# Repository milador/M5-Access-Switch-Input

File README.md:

# M5-Access-Switch-Input

A Bluetooth enabled Adaptive Switch Interface based on ESP32 M5StickC/M5StickCPlus, and the Switch Input module which offers up to two 3.5mm switch inputs. 

The Adaptive Switch Interface includes 4 operating modes: 

    1. Switch Mode
    2. Switch Mac Mode  
    3. Morse Keyboard Mode 
    4. Media Control Mode
    5. Settings Mode
	
The mode can be changed by pressing and holding Switch A for 4 seconds or pressing M5 button.

## Requirements and setup instructions 
The setup process is divided to three main catagories:

  1. [Hardware](./Hardware/) : The required hardware and design files
  2. [Software](./Software/) : The required software
  3. [Documentation](./Documentation/) : The assembly guide,user guide and other documents 

## License

### MIT License

Copyright (c) 2022 milador

Permission is hereby granted, free of charge, to any person obtaining a copy of this software and associated documentation files (the "Software"), to deal in the Software without restriction, including without limitation the rights to use, copy, modify, merge, publish, distribute, sublicense, and/or sell copies of the Software, and to permit persons to whom the Software is furnished to do so, subject to the following conditions:

The above copyright notice and this permission notice shall be included in all copies or substantial portions of the Software.

THE SOFTWARE IS PROVIDED "AS IS", WITHOUT WARRANTY OF ANY KIND, EXPRESS OR IMPLIED, INCLUDING BUT NOT LIMITED TO THE WARRANTIES OF MERCHANTABILITY, FITNESS FOR A PARTICULAR PURPOSE AND NONINFRINGEMENT. IN NO EVENT SHALL THE AUTHORS OR COPYRIGHT HOLDERS BE LIABLE FOR ANY CLAIM, DAMAGES OR OTHER LIABILITY, WHETHER IN AN ACTION OF CONTRACT, TORT OR OTHERWISE, ARISING FROM, OUT OF OR IN CONNECTION WITH THE SOFTWARE OR THE USE OR OTHER DEALINGS IN THE SOFTWARE.

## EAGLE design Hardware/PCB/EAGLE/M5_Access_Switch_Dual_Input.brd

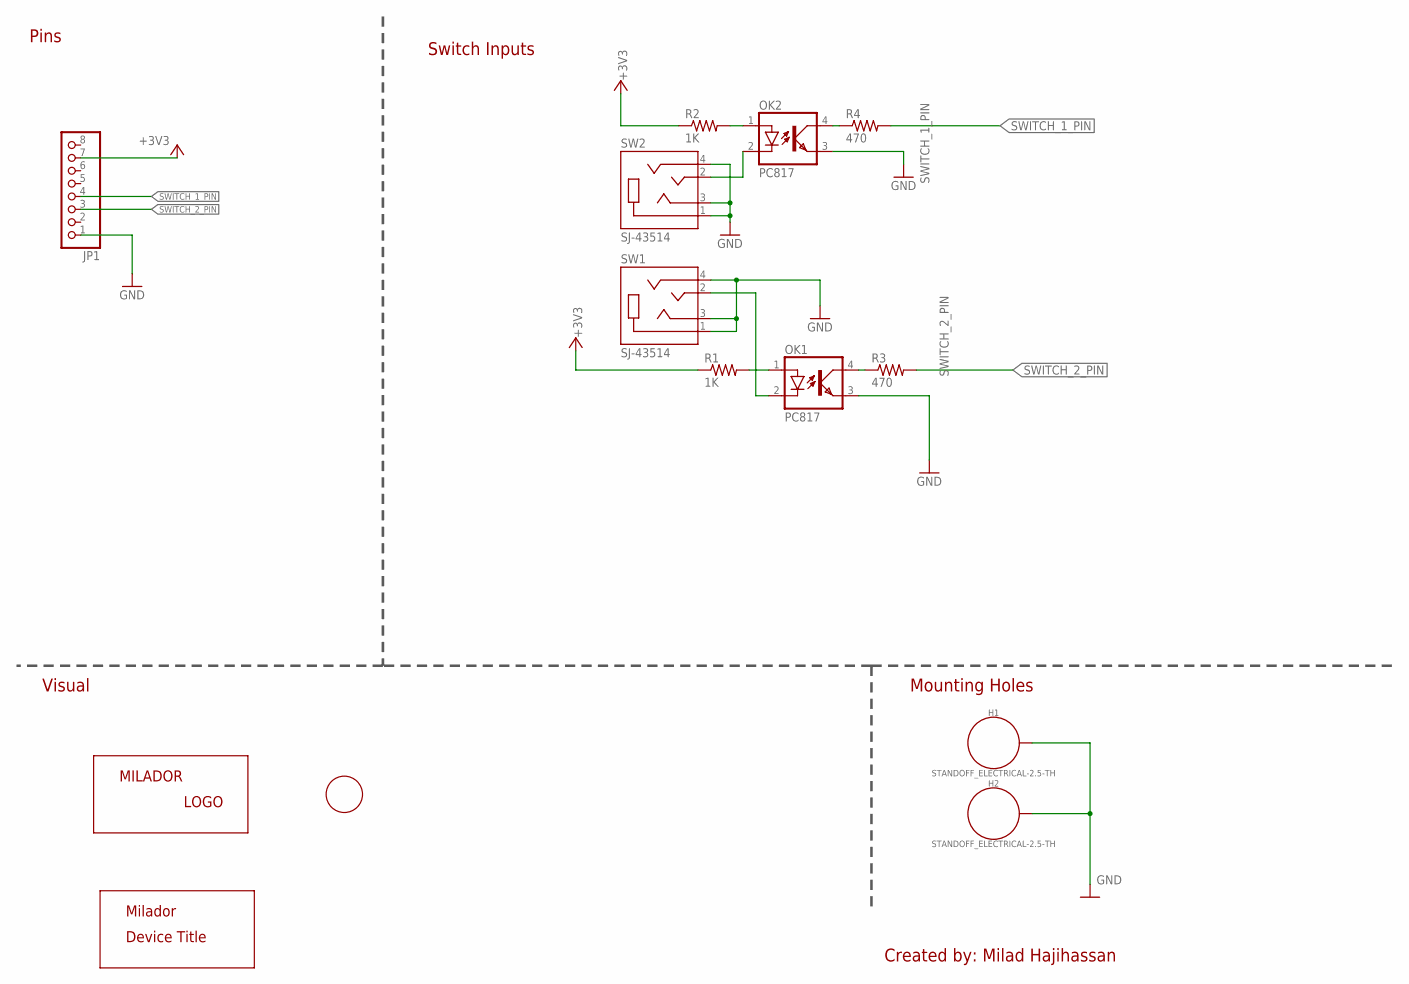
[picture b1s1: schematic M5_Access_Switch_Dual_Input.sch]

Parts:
H1, H2: STANDOFF_ELECTRICAL-2.5-TH; STANDOFF-ELECTRICAL-2.5-TH
JP1: HEADER_MALE-1X8ROUND-RA; 1X08_ROUND_RA
LABEL_DEVICE_TOP: MILADOR-DEVICE-M5-ACCESS-SWITCH; MILADOR_M5_ACCESS_SWITCH
LABEL_INPUT_TOP: MILADOR-SWITCH-NAME-SW-INPUT; SWITCH-INPUT
LABEL_LOGO_TOP: MILADOR-LOGO-SM; MILADOR_LOGO2
OK1, OK2: PC817; DIL04
R1, R2: 1K; RESISTOR_0204/5
R3, R4: 470; RESISTOR_0204/5
SW1, SW2: SJ-43514; CUI_SJ-43514

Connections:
+3V3: JP1.7, R1.1, R2.1
GND: H1.P1, H2.P1, JP1.1, OK1.3 (EMIT), OK2.3 (EMIT), SW1.1 (SLEEVE), SW1.3 (RING1), SW1.4 (RING2), SW2.1 (SLEEVE), SW2.3 (RING1), SW2.4 (RING2)
unnamed: OK1.1 (A), R1.2
unnamed: OK1.4 (COL), R3.1
unnamed: OK1.2 (C), SW1.2 (TIP)
unnamed: OK2.1 (A), R2.2
unnamed: OK2.4 (COL), R4.1
unnamed: OK2.2 (C), SW2.2 (TIP)
SWITCH_1_PIN: JP1.4, R4.2
SWITCH_2_PIN: JP1.3, R3.2

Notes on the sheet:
Switch Inputs
Pins
Mounting Holes
Visual
Created by: Milad Hajihassan

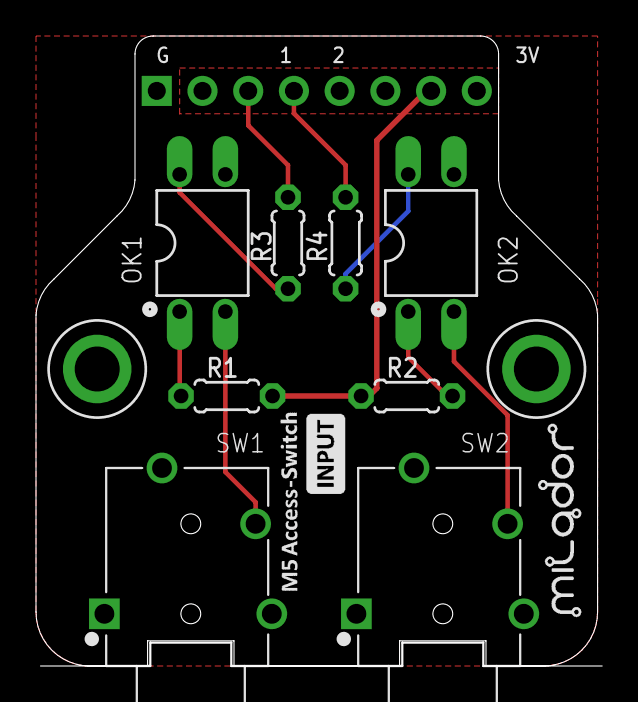
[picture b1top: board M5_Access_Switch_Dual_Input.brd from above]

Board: 2 copper layers, 31.2 x 35.0 mm, 14 parts (1 on the bottom side), 10 nets.

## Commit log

2022-08-20 Added Stereo jack design
2022-08-20 Changed the design to dual mono jacks
2022-08-20 Added Basic software
2022-08-20 Renamed Design files
2022-08-20 Added gerber files
2022-08-29 Added enclosure/case files
2022-08-29 Added BOM
2022-10-01 Updated part list
2022-10-01 Added assembly guide
2022-10-01 Added StickC Code
2022-10-01 Updated the code for M5StickCPlus
2022-10-01 Added image
2022-10-01 Updated code
2022-10-10 Updated code to disable sleep mode
2022-10-10 updated the code
2022-10-10 Updated sleep mode
2022-10-10 Updated user guide
2022-10-11 Added media control mode
